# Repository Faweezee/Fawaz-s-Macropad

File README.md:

# Fawaz's Macropad

A custom 12-key macropad designed to increase productivity while programming or designing, built with the Seeed Xiao RP2040. This project was designed in KiCad (PCB) and Fusion 360 (Case).

|           Schematic            |           PCB           |                   Case                    |
| :----------------------------: | :---------------------: | :---------------------------------------: |
|  |  |  |

## Bill of Materials (BOM)

- 1x Seeed Xiao RP2040
- 12x MX-Style Switches
- 12x White DSA Keycaps
- 12x 1N4148 Diodes (SOD-123 Surface Mount Diodes)
- 3D Printed Case
- 4x M3x16 Bolt

## PCB Design

The PCB uses a standard matrix layout with surface-mount diodes.

## Case Design

The case is a two-part snap-fit design with a dedicated cutout for the USB-C port.

## Firmware

This macropad runs on [KMK Firmware](https://github.com/KMKfw/kmk_firmware) firmware.

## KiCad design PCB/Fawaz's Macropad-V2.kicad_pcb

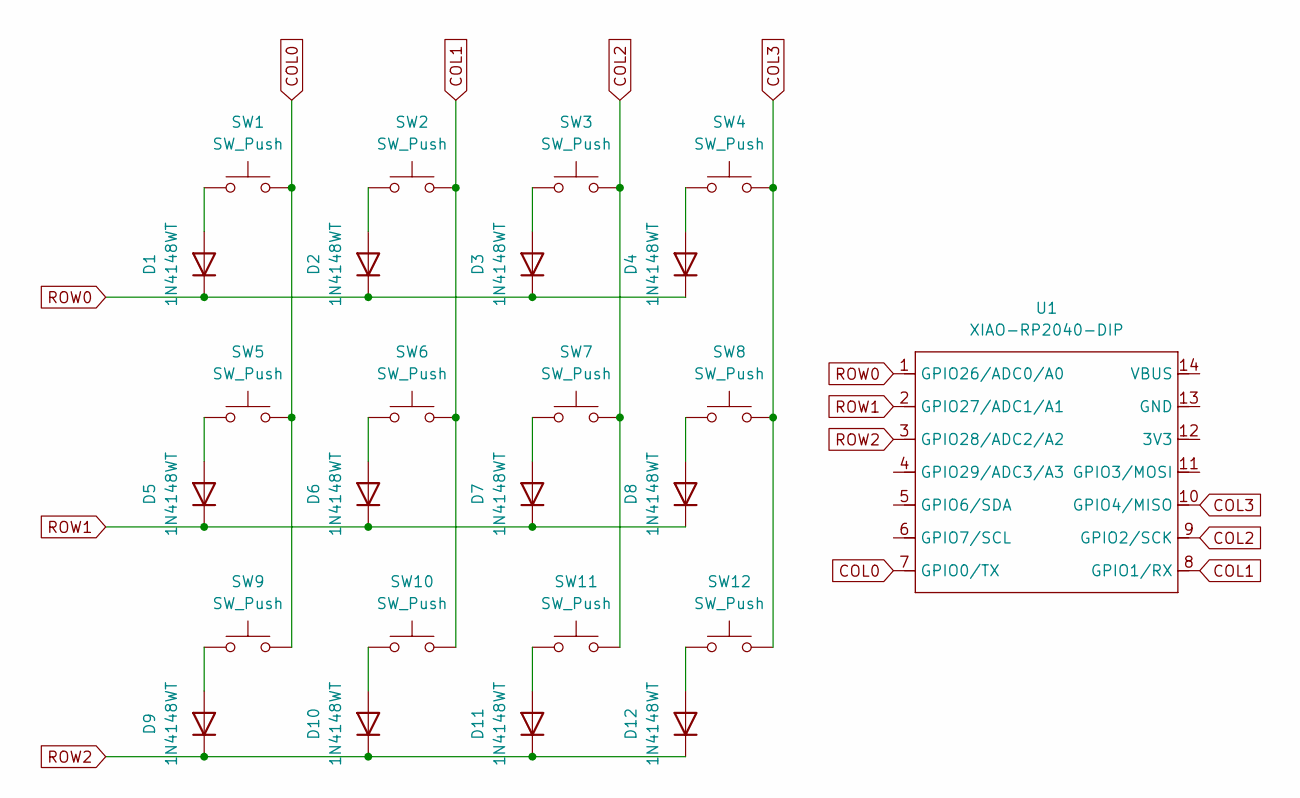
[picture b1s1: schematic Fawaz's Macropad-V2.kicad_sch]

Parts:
D1, D2, D3, D4, D5, D6, D7, D8, D9, D10, D11, D12: 1N4148WT; D_SOD-123
SW1, SW2, SW3, SW4, SW5, SW6, SW7, SW8, SW9, SW10, SW11, SW12: SW_Push; SW_Cherry_MX_1.00u_PCB
U1: XIAO-RP2040-DIP

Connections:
COL0: SW1.2, SW5.2, SW9.2, U1.7 (GPIO0/TX)
COL1: SW2.2, SW6.2, SW10.2, U1.8 (GPIO1/RX)
COL2: SW3.2, SW7.2, SW11.2, U1.9 (GPIO2/SCK)
COL3: SW4.2, SW8.2, SW12.2, U1.10 (GPIO4/MISO)
unnamed: D1.2 (A), SW1.1
unnamed: D2.2 (A), SW2.1
unnamed: D3.2 (A), SW3.1
unnamed: D4.2 (A), SW4.1
unnamed: D5.2 (A), SW5.1
unnamed: D6.2 (A), SW6.1
unnamed: D7.2 (A), SW7.1
unnamed: D8.2 (A), SW8.1
unnamed: D9.2 (A), SW9.1
unnamed: D10.2 (A), SW10.1
unnamed: D11.2 (A), SW11.1
unnamed: D12.2 (A), SW12.1
ROW0: D1.1 (K), D2.1 (K), D3.1 (K), D4.1 (K), U1.1 (GPIO26/ADC0/A0)
ROW1: D5.1 (K), D6.1 (K), D7.1 (K), D8.1 (K), U1.2 (GPIO27/ADC1/A1)
ROW2: D9.1 (K), D10.1 (K), D11.1 (K), D12.1 (K), U1.3 (GPIO28/ADC2/A2)

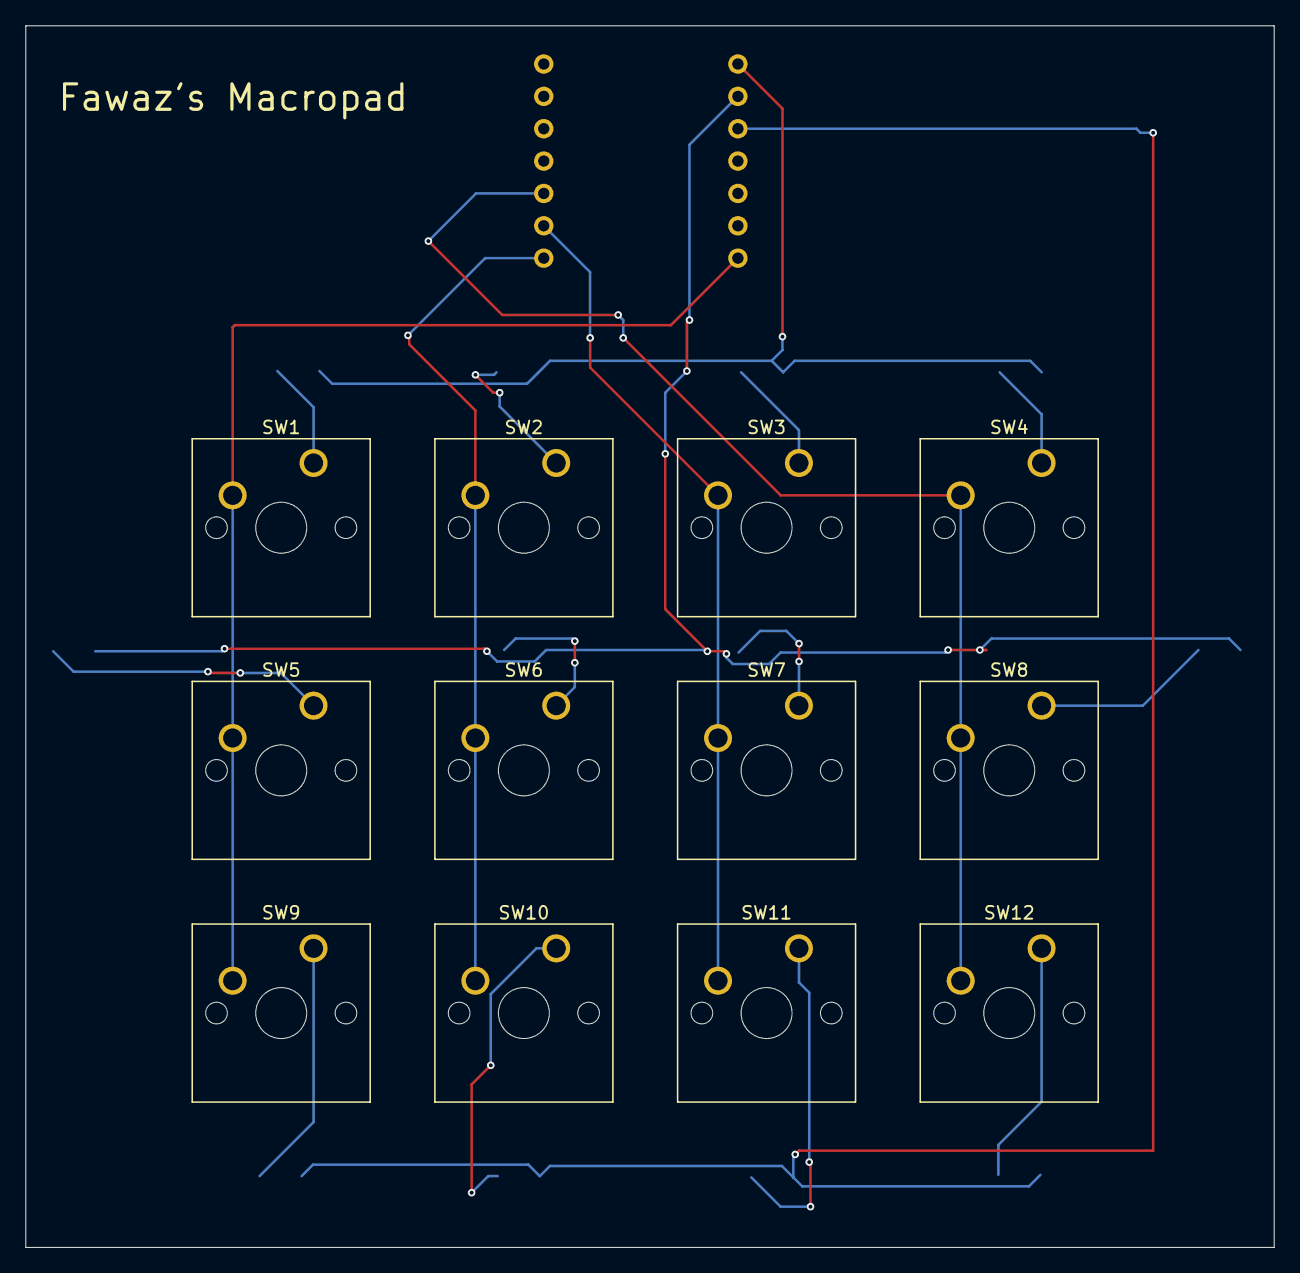
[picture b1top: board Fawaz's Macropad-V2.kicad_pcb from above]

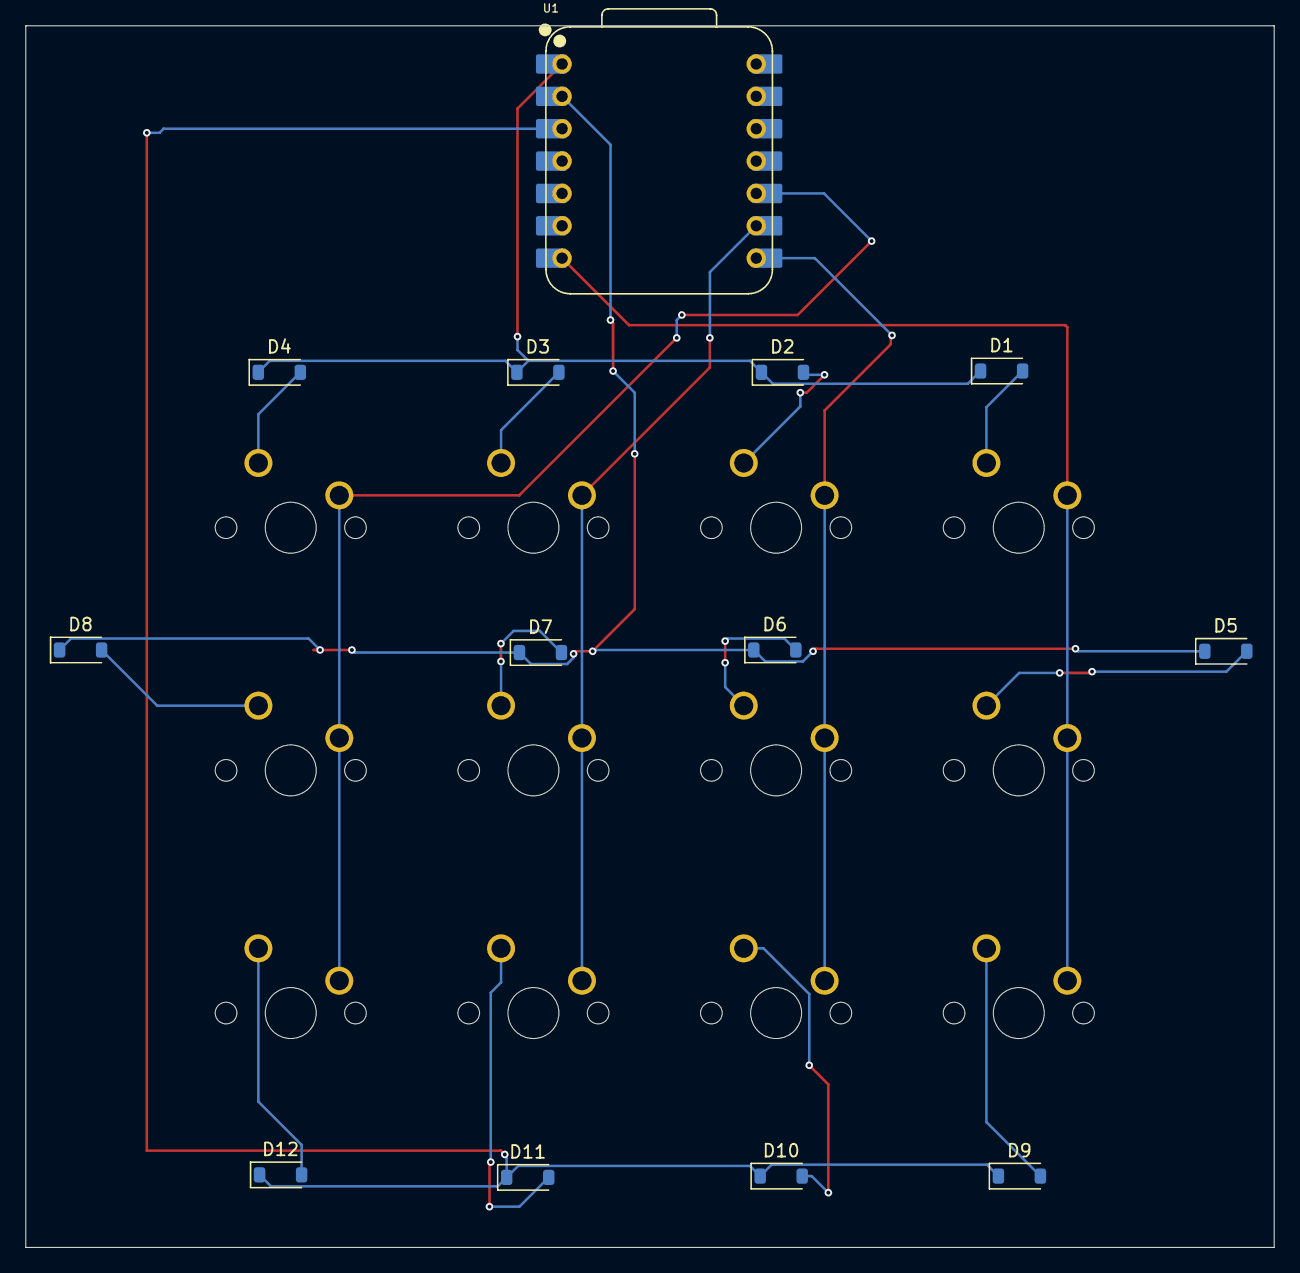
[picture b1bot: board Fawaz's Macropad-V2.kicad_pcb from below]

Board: 2 copper layers, 98.0 x 95.9 mm, 25 parts (13 on the bottom side), 19 nets.

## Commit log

2025-12-16 Updated readme and added files
